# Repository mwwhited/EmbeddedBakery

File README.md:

# Embedded Bakery

## Summary

This is a collection of various electronics and microprocessor projects including PAL, FPGA, CPLD, and microcontroller experiments.

## Repository Structure

```
src/
├── arduino/          # Arduino sketches and libraries
├── AVR/              # AVR microcontroller projects (ATmega, ATtiny)
├── ESP8266/          # ESP8266 WiFi module projects
├── STM32/            # STM32 ARM microcontroller projects
├── PIC/              # Microchip PIC microcontroller projects
├── xilinx/           # Xilinx FPGA projects (Arty A7, Arty Z7)
├── altera/           # Altera/Intel FPGA projects (Cyclone II)
├── GenericFPGA/      # Reusable FPGA IP cores
├── pal/              # Programmable Array Logic projects
├── basicstamp/       # Basic Stamp projects
├── particle/         # Particle IoT projects
└── tools/            # Development tools (.NET solution)
circuits/             # KiCad PCB designs and schematics
notes/                # Reference documentation and datasheets
```

## Key Projects

### Microcontroller Projects
- **Arduino**: Various sensor interfaces, relay controllers, FreeRTOS examples, LANC camera control
- **ESP8266**: LXI Serial Bridge, WiFi relay controllers, network interfaces
- **AVR**: Bare-metal ATmega/ATtiny projects, digital clock
- **STM32**: Blue Pill development projects
- **PIC**: PIC16F627 LED chase patterns

### FPGA Projects
- **Xilinx Arty A7**: MicroBlaze tutorials, custom CPU designs, Pmod interfaces
- **Xilinx Arty Z7**: Zynq HLS tutorials
- **Altera Cyclone II**: Basic FPGA experiments
- **XC9500 CPLD**: Legacy CPLD projects

### PCB Designs
- Analog computer circuits
- Development boards
- Interface adapters (LANC, RS485, H4n)

### Development Tools
- BinaryBaker: ROM/PROM utilities
- MicroCodeBuilder: Custom CPU microcode tools
- TruthExpander: Boolean logic tools

## Getting Started

See individual project README files for specific build instructions.

### Quick Reference

| Platform | Build Tool |
|----------|------------|
| Arduino | Arduino IDE / arduino-cli |
| AVR | WinAVR / avr-gcc + avrdude |
| ESP8266 | PlatformIO / Arduino IDE |
| STM32 | STM32duino / STM32CubeIDE |
| PIC | MPLAB X + XC8 |
| Xilinx | Vivado / ISE |
| Altera | Quartus |
| KiCad | KiCad + KiBot |
| .NET | dotnet CLI / Visual Studio |

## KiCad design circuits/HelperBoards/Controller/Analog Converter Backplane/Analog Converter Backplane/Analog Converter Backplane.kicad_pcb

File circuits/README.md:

# Circuit and PCB Projects

KiCad PCB designs and schematics.

## Projects

### Altair8800
Altair 8800 computer clone PCB.

### AnalogCalculator
Analog computer/calculator circuits including:
- Op-amp based computing boards
- Comdyna GP-6 clone
- Diode function generators
- Fast ADC

### Atmega32DevKit
ATmega32 development kit PCB.

### ComdynaGP6
Comdyna GP-6 analog computer clone components.

### Digital Tools
Digital logic development boards.

### DiodeLogicBoards
Discrete diode logic circuits:
- 1-byte register
- Address decoder (4 to 16)
- Input/output boards
- PROM emulator

### Favero
Favero fencing scoring machine interface.

### HelperBoards
Utility boards:
- 10x10 switch matrix
- Potentiometer boards
- Analog controller boards
- Waveform generator amplifier

### ITT_Phone
Rotary phone interface board.

### MyIOShield
Custom I/O shield PCB.

### Navtec
NavTec interface board.

### Pmod16bitBanked
16-bit banked switch Pmod board.

### PmodLED8x8
8x8 LED matrix Pmod board.

### RC-004 Clone
RC-004 clone circuit.

### SG_Power
Power supply board.

### SimpleClock
Simple clock circuit.

### greaseweazle
Greaseweazle floppy disk interface case/board.

### h4n2rs485
Zoom H4n to RS485 interface.

### i8051
8051 microcontroller development kit.

### lanc2rs485
LANC to RS485 converter.

## KiCad Libraries

### MyCustomSymbols.kicad_sym
Custom schematic symbols.

### MyCustomLibrary.pretty/
Custom PCB footprints.

### KicadSymbols/
Additional symbol libraries.

## Build Documentation

Use KiBot to generate documentation:
```bash
kibot -c ../docs.kibot.yaml
```

## Tools

- **KiCad** - Schematic capture and PCB layout
- **KiBot** - Automated documentation generation

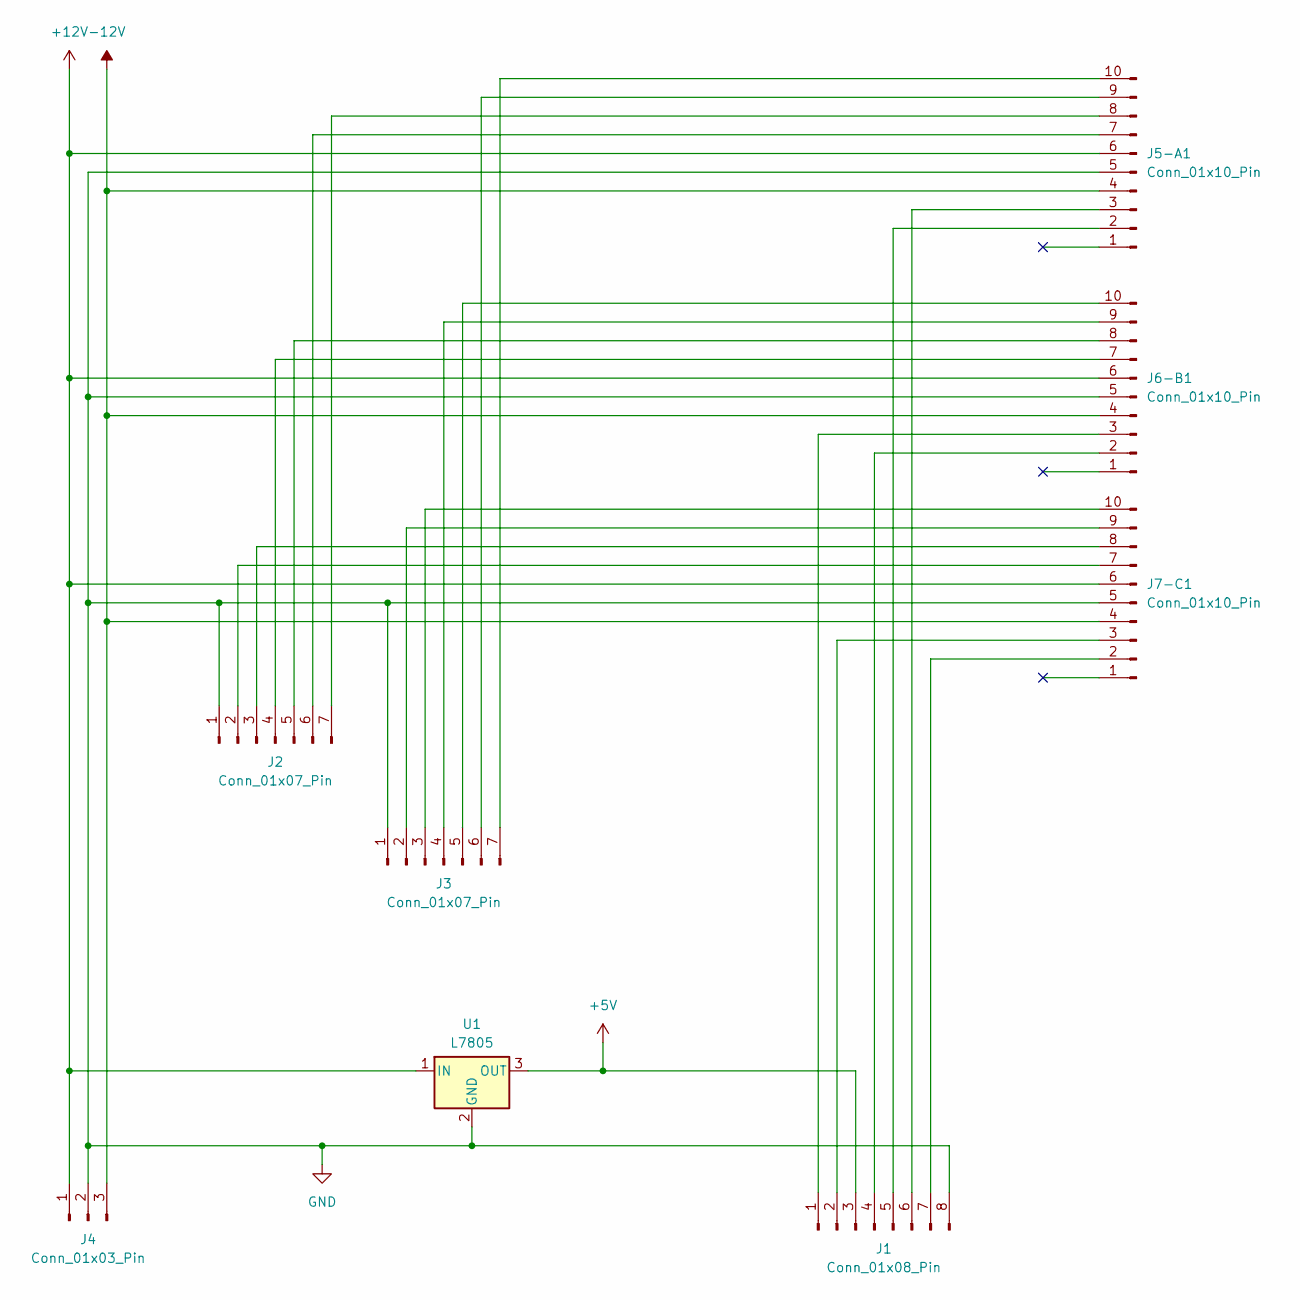
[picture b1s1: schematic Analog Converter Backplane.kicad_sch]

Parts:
J1: Conn_01x08_Pin; PinHeader_1x08_P2.54mm_Vertical
J2, J3: Conn_01x07_Pin; PinHeader_1x07_P2.54mm_Vertical
J4: Conn_01x03_Pin; PinHeader_1x03_P2.54mm_Vertical
J5-A1, J6-B1, J7-C1: Conn_01x10_Pin; PinSocket_1x10_P2.54mm_Vertical
U1: L7805; TO-220-3_Vertical

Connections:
+5V: J1.3, U1.3 (OUT)
+12V: J4.1, J5-A1.6, J6-B1.6, J7-C1.6, U1.1 (IN)
-12V: J4.3, J5-A1.4, J6-B1.4, J7-C1.4
GND: J1.8, J2.1, J3.1, J4.2, J5-A1.5, J6-B1.5, J7-C1.5, U1.2 (GND)
unnamed: J1.1, J6-B1.3
unnamed: J1.2, J7-C1.3
unnamed: J1.4, J6-B1.2
unnamed: J1.5, J5-A1.2
unnamed: J1.6, J5-A1.3
unnamed: J1.7, J7-C1.2
unnamed: J2.2, J7-C1.7
unnamed: J2.3, J7-C1.8
unnamed: J2.4, J6-B1.7
unnamed: J2.5, J6-B1.8
unnamed: J2.6, J5-A1.7
unnamed: J2.7, J5-A1.8
unnamed: J3.2, J7-C1.9
unnamed: J3.3, J7-C1.10
unnamed: J3.4, J6-B1.9
unnamed: J3.5, J6-B1.10
unnamed: J3.6, J5-A1.9
unnamed: J3.7, J5-A1.10

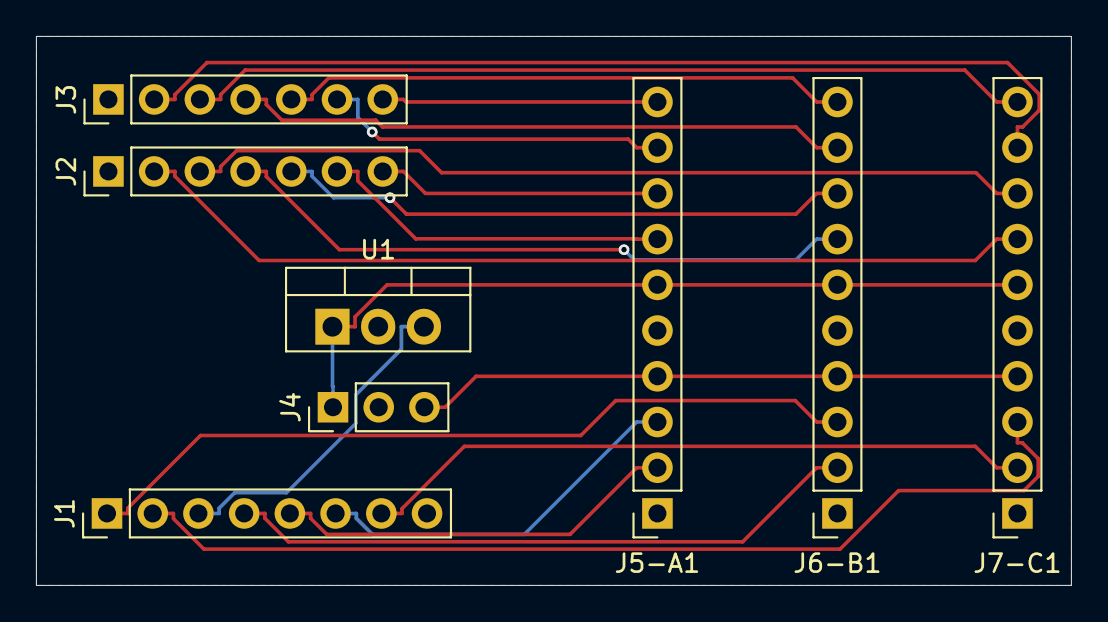
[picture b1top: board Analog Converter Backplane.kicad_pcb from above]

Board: 2 copper layers, 57.5 x 30.5 mm, 8 parts (0 on the bottom side), 22 nets.

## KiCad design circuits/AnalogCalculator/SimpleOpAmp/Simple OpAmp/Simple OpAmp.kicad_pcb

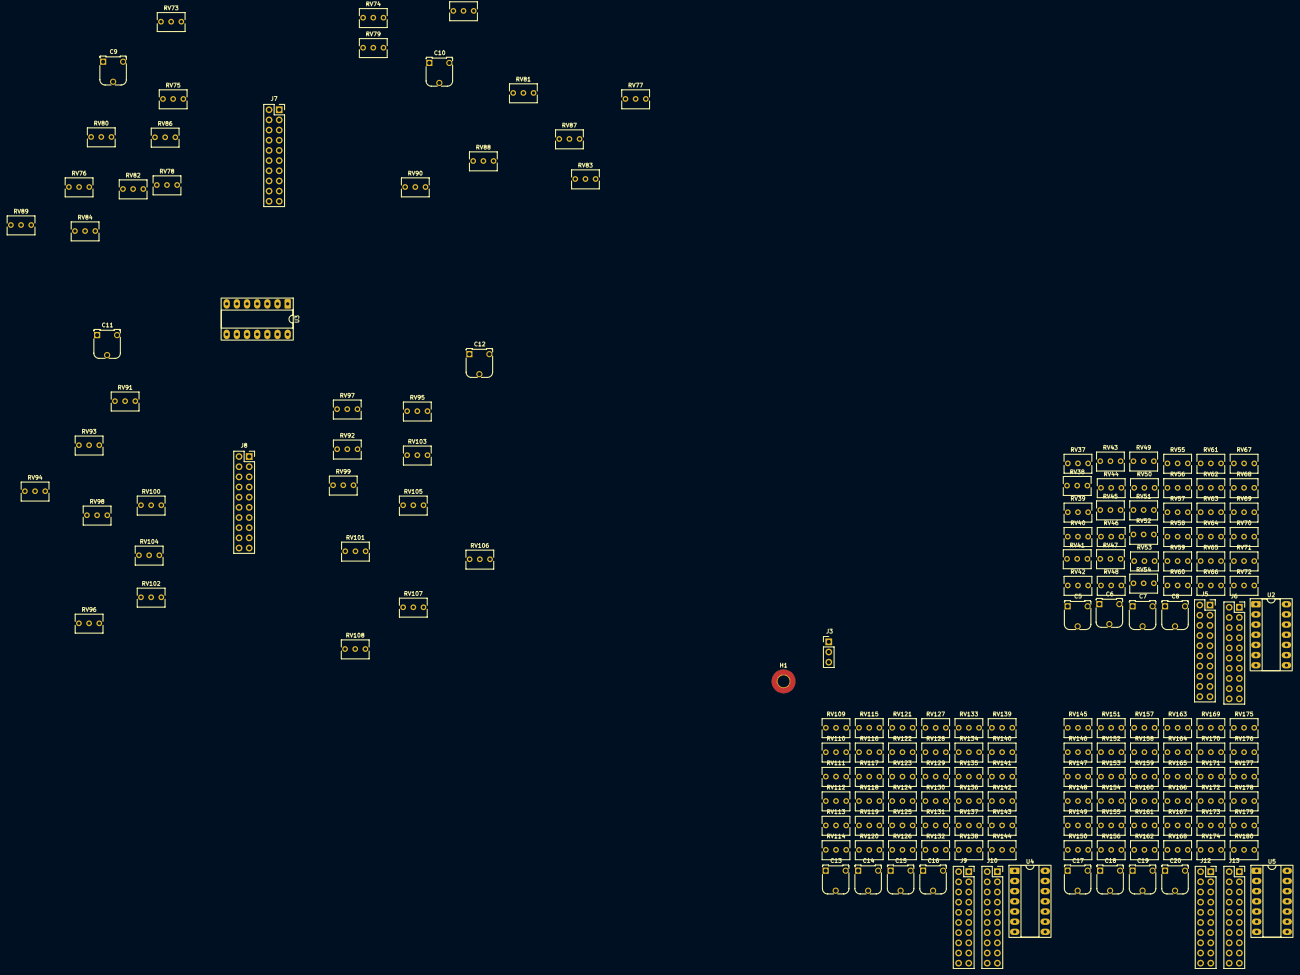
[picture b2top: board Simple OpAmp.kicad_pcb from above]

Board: 2 copper layers, 174 parts (0 on the bottom side), 163 nets, no tracks yet.

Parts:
C5, C6, C7, C8, C9, C10, C11, C12, C13, C14, C15, C16, C17, C18, C19, C20: C_Trim_Differential; Potentiometer_Runtron_RM-065_Vertical
H1: MountingHole_3mm_Pad_TopBottom
J3: Conn_01x03_Pin; PinHeader_1x03_P2.54mm_Vertical
J5, J6, J7, J8, J9, J10, J12, J13: Conn_02x10_Odd_Even; PinSocket_2x10_P2.54mm_Vertical
RV37, RV38, RV39, RV40, RV41, RV42, RV43, RV44, RV45, RV46, RV47, RV48, RV49, RV50, RV51, RV52, RV53, RV54, RV55, RV56, RV57, RV58, RV59, RV60, RV61, RV62, RV63, RV64, RV65, RV66, RV67, RV68, RV69, RV70, RV71, RV72, RV73, RV74, RV75, RV76, RV77, RV78, RV79, RV80, RV81, RV82, RV83, RV84, RV85, RV86, RV87, RV88, RV89, RV90, RV91, RV92, RV93, RV94, RV95, RV96, RV97, RV98, RV99, RV100, RV101, RV102, RV103, RV104, RV105, RV106, RV107, RV108, RV109, RV110, RV111, RV112, RV113, RV114, RV115, RV116, RV117, RV118, RV119, RV120, RV121, RV122, RV123, RV124, RV125, RV126, RV127, RV128, RV129, RV130, RV131, RV132, RV133, RV134, RV135, RV136, RV137, RV138, RV139, RV140, RV141, RV142, RV143, RV144, RV145, RV146, RV147, RV148, RV149, RV150, RV151, RV152, RV153, RV154, RV155, RV156, RV157, RV158, RV159, RV160, RV161, RV162, RV163, RV164, RV165, RV166, RV167, RV168, RV169, RV170, RV171, RV172, RV173, RV174, RV175, RV176, RV177, RV178, RV179, RV180: R_Potentiometer_US; Potentiometer_Bourns_3266Y_Vertical
U2, U3, U4, U5: Opamp_Quad; DIP-14_W7.62mm_Socket_LongPads

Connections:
+15V: J3.1, U2.4 (V+), U3.4 (V+), U4.4 (V+), U5.4 (V+)
-15V: J3.3, U2.11 (V-), U3.11 (V-), U4.11 (V-), U5.11 (V-)
GND: H1.1, J3.2, U2.2 (-), U2.6 (-), U2.9 (-), U2.13 (-), U3.2 (-), U3.6 (-), U3.9 (-), U3.13 (-), U4.2 (-), U4.6 (-), U4.9 (-), U4.13 (-), U5.2 (-), U5.6 (-), U5.9 (-), U5.13 (-)
unnamed: J5.1, RV38.3
unnamed: C5.2, J5.2, RV37.2, U2.7
unnamed: J5.3, RV41.3
unnamed: C5.1, J5.4, RV37.3, RV39.2, RV40.2, RV42.2, RV44.2, RV46.2, RV48.2, RV50.2, RV53.2, U2.5 (+)
unnamed: J5.5, RV43.3
unnamed: J5.6, RV39.3
unnamed: J5.7, RV45.3
unnamed: J5.8, RV40.3
unnamed: J5.9, RV47.3
unnamed: J5.10, RV42.3
unnamed: J5.11, RV49.3
unnamed: J5.12, RV44.3
unnamed: J5.13, RV51.3
unnamed: J5.14, RV46.3
unnamed: J5.15, RV52.3
unnamed: J5.16, RV48.3
unnamed: C6.1, J5.17, RV38.2, RV41.2, RV43.2, RV45.2, RV47.2, RV49.2, RV51.2, RV52.2, RV54.3, U2.3 (+)
unnamed: J5.18, RV50.3
unnamed: C6.2, J5.19, RV54.2, U2.1
unnamed: J5.20, RV53.3
unnamed: J6.1, RV56.3
unnamed: C7.2, J6.2, RV55.2, U2.14
unnamed: J6.3, RV59.3
unnamed: C7.1, J6.4, RV55.3, RV57.2, RV58.2, RV60.2, RV62.2, RV64.2, RV66.2, RV68.2, RV71.2, U2.12 (+)
unnamed: J6.5, RV61.3
unnamed: J6.6, RV57.3
unnamed: J6.7, RV63.3
unnamed: J6.8, RV58.3
unnamed: J6.9, RV65.3
unnamed: J6.10, RV60.3
unnamed: J6.11, RV67.3
unnamed: J6.12, RV62.3
unnamed: J6.13, RV69.3
unnamed: J6.14, RV64.3
unnamed: J6.15, RV70.3
unnamed: J6.16, RV66.3
unnamed: C8.1, J6.17, RV56.2, RV59.2, RV61.2, RV63.2, RV65.2, RV67.2, RV69.2, RV70.2, RV72.3, U2.10 (+)
unnamed: J6.18, RV68.3
unnamed: C8.2, J6.19, RV72.2, U2.8
unnamed: J6.20, RV71.3
unnamed: J7.1, RV74.3
unnamed: C9.2, J7.2, RV73.2, U3.7
unnamed: J7.3, RV77.3
unnamed: C9.1, J7.4, RV73.3, RV75.2, RV76.2, RV78.2, RV80.2, RV82.2, RV84.2, RV86.2, RV89.2, U3.5 (+)
unnamed: J7.5, RV79.3
unnamed: J7.6, RV75.3
unnamed: J7.7, RV81.3
unnamed: J7.8, RV76.3
unnamed: J7.9, RV83.3
unnamed: J7.10, RV78.3
unnamed: J7.11, RV85.3
unnamed: J7.12, RV80.3
unnamed: J7.13, RV87.3
unnamed: J7.14, RV82.3
unnamed: J7.15, RV88.3
unnamed: J7.16, RV84.3
unnamed: C10.1, J7.17, RV74.2, RV77.2, RV79.2, RV81.2, RV83.2, RV85.2, RV87.2, RV88.2, RV90.3, U3.3 (+)
unnamed: J7.18, RV86.3
unnamed: C10.2, J7.19, RV90.2, U3.1
unnamed: J7.20, RV89.3
unnamed: J8.1, RV92.3
unnamed: C11.2, J8.2, RV91.2, U3.14
unnamed: J8.3, RV95.3
unnamed: C11.1, J8.4, RV91.3, RV93.2, RV94.2, RV96.2, RV98.2, RV100.2, RV102.2, RV104.2, RV107.2, U3.12 (+)
unnamed: J8.5, RV97.3
unnamed: J8.6, RV93.3
unnamed: J8.7, RV99.3
unnamed: J8.8, RV94.3
unnamed: J8.9, RV101.3
unnamed: J8.10, RV96.3
unnamed: J8.11, RV103.3
unnamed: J8.12, RV98.3
unnamed: J8.13, RV105.3
unnamed: J8.14, RV100.3
unnamed: J8.15, RV106.3
unnamed: J8.16, RV102.3
unnamed: C12.1, J8.17, RV92.2, RV95.2, RV97.2, RV99.2, RV101.2, RV103.2, RV105.2, RV106.2, RV108.3, U3.10 (+)
unnamed: J8.18, RV104.3
unnamed: C12.2, J8.19, RV108.2, U3.8
unnamed: J8.20, RV107.3
unnamed: J9.1, RV110.3
unnamed: C13.2, J9.2, RV109.2, U4.7
unnamed: J9.3, RV113.3
unnamed: C13.1, J9.4, RV109.3, RV111.2, RV112.2, RV114.2, RV116.2, RV118.2, RV120.2, RV122.2, RV125.2, U4.5 (+)
unnamed: J9.5, RV115.3
unnamed: J9.6, RV111.3
unnamed: J9.7, RV117.3
unnamed: J9.8, RV112.3
unnamed: J9.9, RV119.3
unnamed: J9.10, RV114.3
unnamed: J9.11, RV121.3
unnamed: J9.12, RV116.3
unnamed: J9.13, RV123.3
unnamed: J9.14, RV118.3
unnamed: J9.15, RV124.3
unnamed: J9.16, RV120.3
unnamed: C14.1, J9.17, RV110.2, RV113.2, RV115.2, RV117.2, RV119.2, RV121.2, RV123.2, RV124.2, RV126.3, U4.3 (+)
unnamed: J9.18, RV122.3
unnamed: C14.2, J9.19, RV126.2, U4.1
unnamed: J9.20, RV125.3
unnamed: J10.1, RV128.3
unnamed: C15.2, J10.2, RV127.2, U4.14
unnamed: J10.3, RV131.3
unnamed: C15.1, J10.4, RV127.3, RV129.2, RV130.2, RV132.2, RV134.2, RV136.2, RV138.2, RV140.2, RV143.2, U4.12 (+)
unnamed: J10.5, RV133.3
unnamed: J10.6, RV129.3
unnamed: J10.7, RV135.3
unnamed: J10.8, RV130.3
unnamed: J10.9, RV137.3
unnamed: J10.10, RV132.3
unnamed: J10.11, RV139.3
unnamed: J10.12, RV134.3
unnamed: J10.13, RV141.3
unnamed: J10.14, RV136.3
unnamed: J10.15, RV142.3
unnamed: J10.16, RV138.3
unnamed: C16.1, J10.17, RV128.2, RV131.2, RV133.2, RV135.2, RV137.2, RV139.2, RV141.2, RV142.2, RV144.3, U4.10 (+)
unnamed: J10.18, RV140.3
unnamed: C16.2, J10.19, RV144.2, U4.8
unnamed: J10.20, RV143.3
unnamed: J12.1, RV146.3
unnamed: C17.2, J12.2, RV145.2, U5.7
unnamed: J12.3, RV149.3
unnamed: C17.1, J12.4, RV145.3, RV147.2, RV148.2, RV150.2, RV152.2, RV154.2, RV156.2, RV158.2, RV161.2, U5.5 (+)
unnamed: J12.5, RV151.3
unnamed: J12.6, RV147.3
unnamed: J12.7, RV153.3
unnamed: J12.8, RV148.3
unnamed: J12.9, RV155.3
unnamed: J12.10, RV150.3
unnamed: J12.11, RV157.3
unnamed: J12.12, RV152.3
unnamed: J12.13, RV159.3
unnamed: J12.14, RV154.3
unnamed: J12.15, RV160.3
unnamed: J12.16, RV156.3
unnamed: C18.1, J12.17, RV146.2, RV149.2, RV151.2, RV153.2, RV155.2, RV157.2, RV159.2, RV160.2, RV162.3, U5.3 (+)
unnamed: J12.18, RV158.3
unnamed: C18.2, J12.19, RV162.2, U5.1
unnamed: J12.20, RV161.3
unnamed: J13.1, RV164.3
unnamed: C19.2, J13.2, RV163.2, U5.14
unnamed: J13.3, RV167.3
unnamed: C19.1, J13.4, RV163.3, RV165.2, RV166.2, RV168.2, RV170.2, RV172.2, RV174.2, RV176.2, RV179.2, U5.12 (+)
unnamed: J13.5, RV169.3
unnamed: J13.6, RV165.3
unnamed: J13.7, RV171.3
unnamed: J13.8, RV166.3
unnamed: J13.9, RV173.3
unnamed: J13.10, RV168.3
unnamed: J13.11, RV175.3
unnamed: J13.12, RV170.3
unnamed: J13.13, RV177.3
unnamed: J13.14, RV172.3
unnamed: J13.15, RV178.3
unnamed: J13.16, RV174.3
unnamed: C20.1, J13.17, RV164.2, RV167.2, RV169.2, RV171.2, RV173.2, RV175.2, RV177.2, RV178.2, RV180.3, U5.10 (+)
unnamed: J13.18, RV176.3
unnamed: C20.2, J13.19, RV180.2, U5.8
unnamed: J13.20, RV179.3

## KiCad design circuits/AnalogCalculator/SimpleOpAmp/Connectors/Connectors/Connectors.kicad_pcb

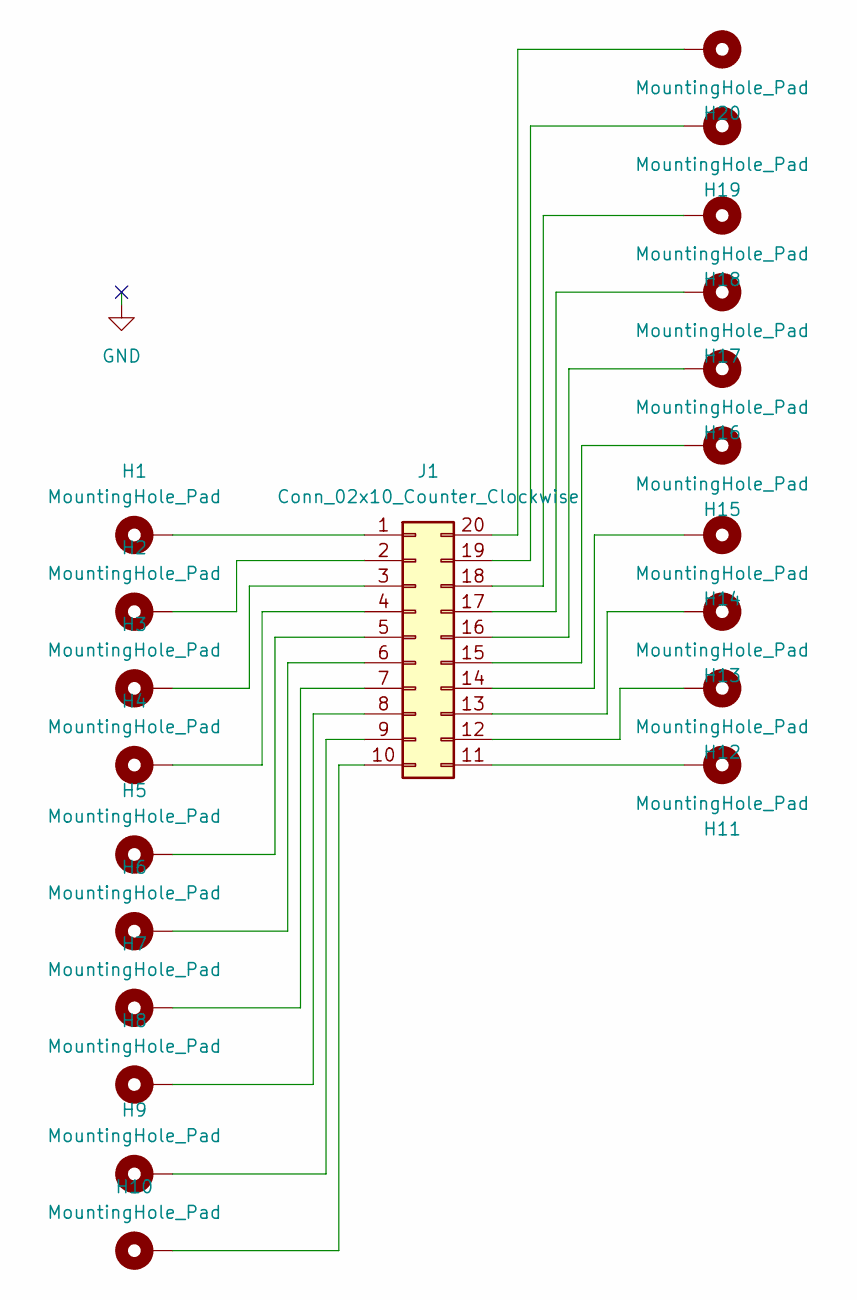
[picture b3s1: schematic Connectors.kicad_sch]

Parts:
H1, H2, H3, H4, H5, H6, H7, H8, H9, H10, H11, H12, H13, H14, H15, H16, H17, H18, H19, H20: MountingHole_Pad; MountingHole_2.2mm_M2_DIN965_Pad
J1: Conn_02x10_Counter_Clockwise; PinHeader_2x10_P2.54mm_Vertical

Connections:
unnamed: H1.1, J1.1
unnamed: H2.1, J1.2
unnamed: H3.1, J1.3
unnamed: H4.1, J1.4
unnamed: H5.1, J1.5
unnamed: H6.1, J1.6
unnamed: H7.1, J1.7
unnamed: H8.1, J1.8
unnamed: H9.1, J1.9
unnamed: H10.1, J1.10
unnamed: H11.1, J1.11
unnamed: H12.1, J1.12
unnamed: H13.1, J1.13
unnamed: H14.1, J1.14
unnamed: H15.1, J1.15
unnamed: H16.1, J1.16
unnamed: H17.1, J1.17
unnamed: H18.1, J1.18
unnamed: H19.1, J1.19
unnamed: H20.1, J1.20

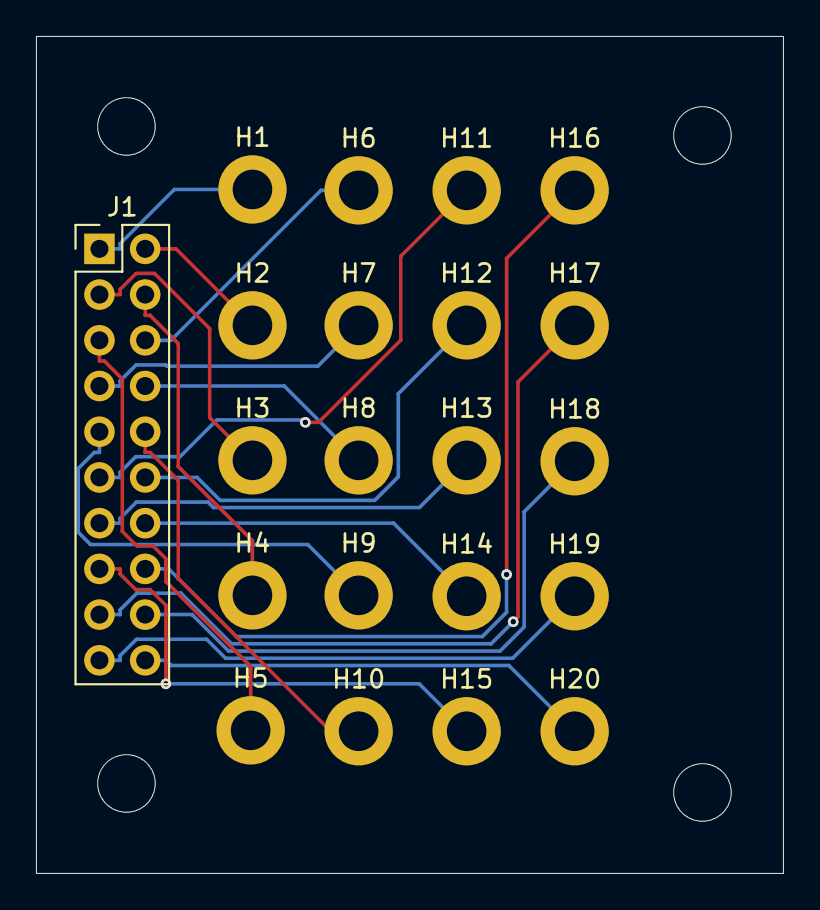
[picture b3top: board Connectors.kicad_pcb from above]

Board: 2 copper layers, 41.5 x 46.5 mm, 25 parts (0 on the bottom side), 20 nets.

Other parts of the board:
REF1, REF2, REF3, REF4: MountingHole_3.2mm_M3

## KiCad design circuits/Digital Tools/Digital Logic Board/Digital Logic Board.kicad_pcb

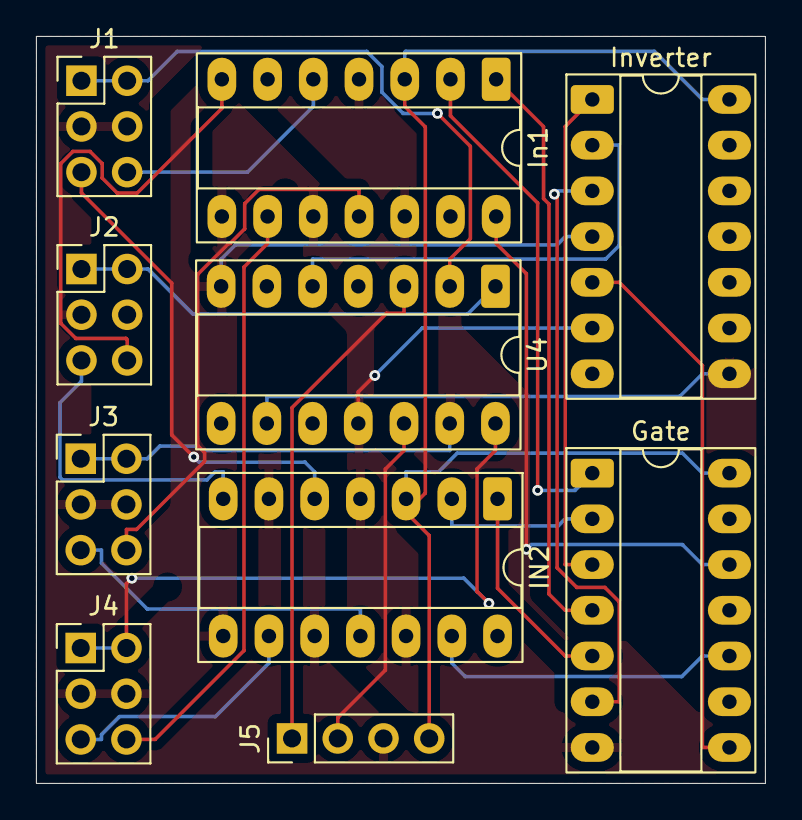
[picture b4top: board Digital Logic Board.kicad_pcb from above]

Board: 2 copper layers, 40.5 x 41.5 mm, 10 parts (0 on the bottom side), 32 nets.

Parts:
Gate: 74LS32; DIP-14_W7.62mm_Socket_LongPads
IN2: LM339; DIP-14_W7.62mm_Socket_LongPads
In1: LM339; DIP-14_W7.62mm_Socket_LongPads
Inverter: 74HC14; DIP-14_W7.62mm_Socket_LongPads
J1, J2, J3, J4: Conn_02x03_Counter_Clockwise; PinHeader_2x03_P2.54mm_Vertical
J5: Conn_01x04_Pin; PinHeader_1x04_P2.54mm_Vertical
U4: LM339; DIP-14_W7.62mm_Socket_LongPads

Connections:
+5V: Gate.14 (VCC), IN2.3 (V+), In1.3 (V+), Inverter.14 (VCC), J5.4
+10V: J5.1, U4.3 (V+)
-10V: J5.2, U4.12 (V-)
GND: Gate.7 (GND), IN2.4 (-), IN2.6 (-), IN2.8 (-), IN2.10 (-), IN2.12 (V-), In1.4 (-), In1.6 (-), In1.8 (-), In1.10 (-), In1.12 (V-), Inverter.7 (GND), Inverter.11, Inverter.13, J1.3, J1.4, J2.3, J2.4, J3.3, J3.4, J4.3, J4.4, J5.3, U4.4 (-), U4.6 (-), U4.8 (-), U4.10 (-)
unnamed: J1.1, J1.2, U4.2
unnamed: IN2.5 (+), J1.5
unnamed: In1.5 (+), J1.6
unnamed: J2.1, J2.2, U4.1
unnamed: IN2.7 (+), J2.5
unnamed: In1.7 (+), J2.6
unnamed: J3.1, J3.2, U4.13
unnamed: IN2.11 (+), J3.5
unnamed: In1.11 (+), J3.6
unnamed: J4.1, J4.2, U4.14
unnamed: IN2.9 (+), J4.5
unnamed: In1.9 (+), J4.6
unnamed: Gate.4, In1.1
unnamed: Gate.1, In1.2
unnamed: Gate.9, In1.13
unnamed: Gate.12, In1.14
unnamed: Gate.3, Inverter.1
unnamed: Gate.6, Inverter.3
unnamed: Gate.8, Inverter.5
unnamed: Gate.11, Inverter.9
unnamed: Gate.5, IN2.1
unnamed: Gate.2, IN2.2
unnamed: Gate.10, IN2.13
unnamed: Gate.13, IN2.14
unnamed: Inverter.2, U4.5 (+)
unnamed: Inverter.4, U4.7 (+)
unnamed: Inverter.6, U4.11 (+)
unnamed: Inverter.8, U4.9 (+)

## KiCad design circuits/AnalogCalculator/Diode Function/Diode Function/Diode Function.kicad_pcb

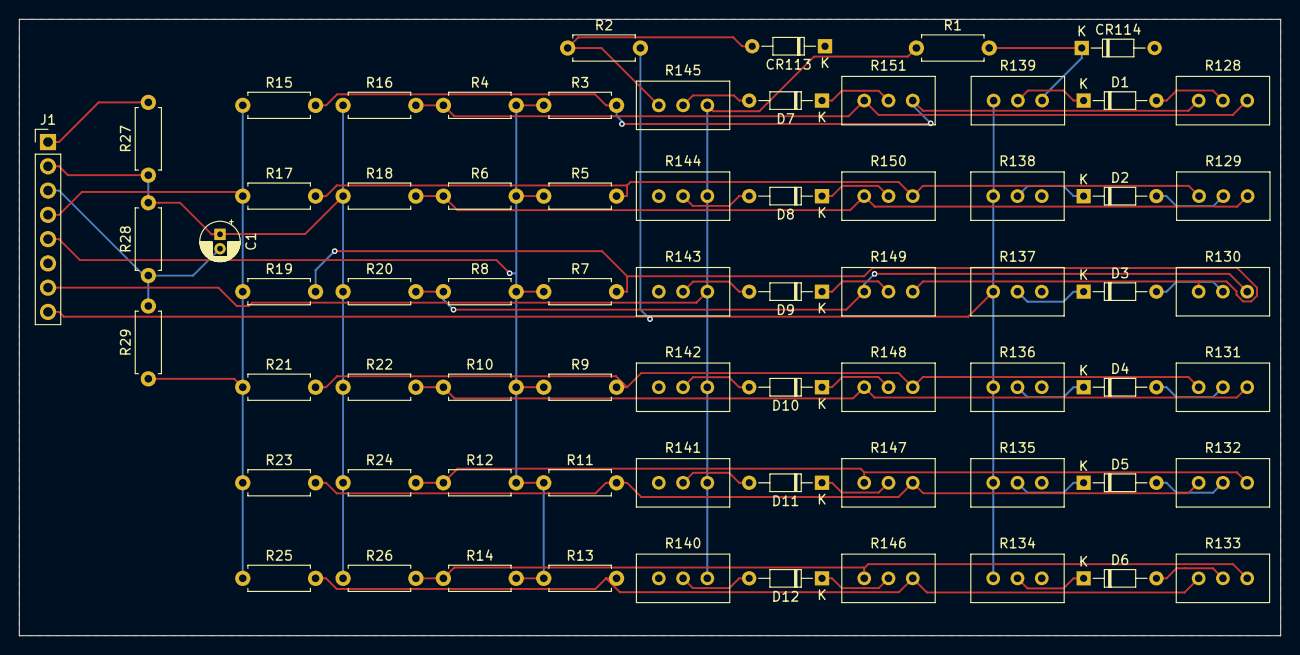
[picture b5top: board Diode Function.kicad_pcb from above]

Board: 2 copper layers, 132.0 x 64.5 mm, 69 parts (0 on the bottom side), 46 nets.

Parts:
C1: 27pF; CP_Radial_D4.0mm_P1.50mm
CR113, CR114: 1N459; D_DO-34_SOD68_P7.62mm_Horizontal
D1, D2, D3, D4, D5, D6, D7, D8, D9, D10, D11, D12: 1N459; D_DO-34_SOD68_P7.62mm_Horizontal
J1: Conn_01x08_Pin; PinHeader_1x08_P2.54mm_Vertical
R1, R2: 68k; R_Axial_DIN0207_L6.3mm_D2.5mm_P7.62mm_Horizontal
R3, R4, R5, R6, R7, R8, R9, R10, R11, R12, R13, R14: 250k; R_Axial_DIN0207_L6.3mm_D2.5mm_P7.62mm_Horizontal
R15, R16, R17, R18, R19, R20, R21, R22, R23, R24, R25, R26: 634k; R_Axial_DIN0207_L6.3mm_D2.5mm_P7.62mm_Horizontal
R27: 1M; R_Axial_DIN0207_L6.3mm_D2.5mm_P7.62mm_Horizontal
R28, R29: 100k; R_Axial_DIN0207_L6.3mm_D2.5mm_P7.62mm_Horizontal
R128, R129, R130, R131, R132, R133, R146, R147, R148, R149, R150, R151: 250k; Potentiometer_Bourns_3296W_Vertical
R134, R135, R136, R137, R138, R139, R140, R141, R142, R143, R144, R145: 100k; Potentiometer_Bourns_3296W_Vertical

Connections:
/+100V: J1.8, R2.2, R134.3, R135.3, R136.3, R137.3, R138.3, R139.3
/-100V: J1.7, R1.1, R140.1, R141.1, R142.1, R143.1, R144.1, R145.1
/Input: J1.5, R3.1, R4.2, R5.1, R6.2, R7.1, R8.2, R9.1, R10.2, R11.1, R12.2, R13.1, R14.2
/Junction 1: J1.4, R15.1, R17.1, R19.1, R21.1, R23.1, R25.1, R29.1
/Junction 2: C1.1, J1.2, R16.1, R18.1, R20.1, R22.1, R24.1, R26.1, R27.1, R28.2
/Output 1: C1.2, J1.3, R28.1, R29.2
/Output 2: J1.1, R27.2
GND: CR113.1 (K), CR114.2 (A), J1.6, R134.1, R135.1, R136.1, R137.1, R138.1, R140.3, R141.3, R142.3, R143.3, R144.3
unnamed: CR113.2 (A), R2.1, R145.3
unnamed: CR114.1 (K), R1.2, R139.1
unnamed: D1.2 (A), R128.2
unnamed: D1.1 (K), R139.2
unnamed: D2.2 (A), R129.2
unnamed: D2.1 (K), R138.2
unnamed: D3.2 (A), R130.2
unnamed: D3.1 (K), R137.2
unnamed: D4.2 (A), R131.2
unnamed: D4.1 (K), R136.2
unnamed: D5.2 (A), R132.2
unnamed: D5.1 (K), R135.2
unnamed: D6.2 (A), R133.2
unnamed: D6.1 (K), R134.2
unnamed: D7.2 (A), R145.2
unnamed: D7.1 (K), R151.2
unnamed: D8.2 (A), R144.2
unnamed: D8.1 (K), R150.2
unnamed: D9.2 (A), R143.2
unnamed: D9.1 (K), R149.2
unnamed: D10.2 (A), R142.2
unnamed: D10.1 (K), R148.2
unnamed: D11.2 (A), R141.2
unnamed: D11.1 (K), R147.2
unnamed: D12.2 (A), R140.2
unnamed: D12.1 (K), R146.2
unnamed: R10.1, R22.2, R131.1, R148.3
unnamed: R11.2, R23.2, R132.3, R147.1
unnamed: R12.1, R24.2, R132.1, R147.3
unnamed: R13.2, R25.2, R133.3, R146.1
unnamed: R4.1, R16.2, R128.1, R151.3
unnamed: R3.2, R15.2, R128.3, R151.1
unnamed: R6.1, R18.2, R129.1, R150.3
unnamed: R5.2, R17.2, R129.3, R150.1
unnamed: R8.1, R20.2, R130.1, R149.3
unnamed: R7.2, R19.2, R130.3, R149.1
unnamed: R9.2, R21.2, R131.3, R148.1
unnamed: R14.1, R26.2, R133.1, R146.3

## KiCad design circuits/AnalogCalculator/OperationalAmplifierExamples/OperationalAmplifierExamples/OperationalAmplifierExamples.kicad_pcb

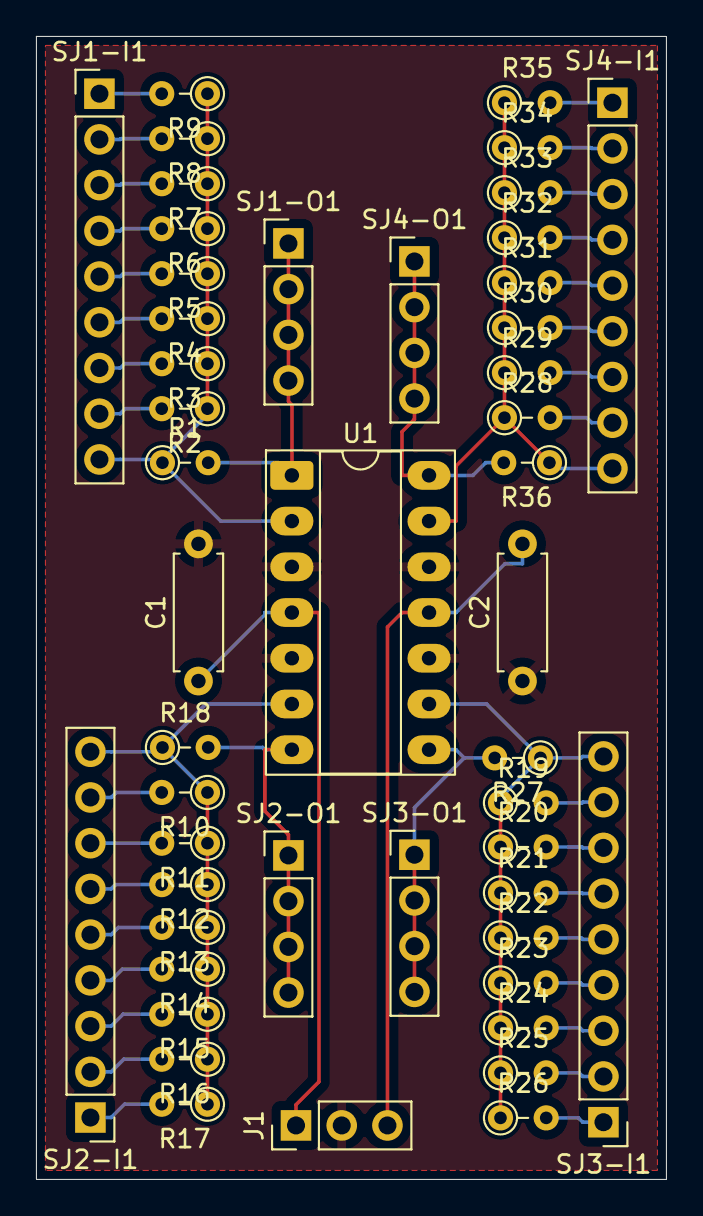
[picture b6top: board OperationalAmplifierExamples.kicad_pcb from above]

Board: 2 copper layers, 35.0 x 63.5 mm, 48 parts (0 on the bottom side), 43 nets.

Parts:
C1, C2: 100nf; R_Axial_DIN0207_L6.3mm_D2.5mm_P7.62mm_Horizontal
J1: Conn_01x03_Pin; PinHeader_1x03_P2.54mm_Vertical
R1, R2, R3, R4, R5, R10, R11, R12, R13, R18, R19, R20, R21, R22, R27, R28, R29, R30, R31, R36: 100k; R_Axial_DIN0204_L3.6mm_D1.6mm_P2.54mm_Vertical
R6, R7, R14, R15, R23, R24, R32, R33: 10k; R_Axial_DIN0204_L3.6mm_D1.6mm_P2.54mm_Vertical
R8, R9, R16, R17, R25, R26, R34, R35: 1M; R_Axial_DIN0204_L3.6mm_D1.6mm_P2.54mm_Vertical
SJ1-I1, SJ2-I1, SJ3-I1, SJ4-I1: Conn_01x09; PinHeader_1x09_P2.54mm_Vertical
SJ1-O1, SJ2-O1, SJ3-O1, SJ4-O1: Conn_01x04_Pin; PinHeader_1x04_P2.54mm_Vertical
U1: LM324; DIP-14_W7.62mm_Socket_LongPads

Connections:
+15V: C1.1, J1.1, U1.4 (V+)
-15V: C2.2, J1.3, U1.11 (V-)
/Inverting Summer/S1-1-1: R2.2, SJ1-I1.8
/Inverting Summer/S1-1-2: R3.2, SJ1-I1.7
/Inverting Summer/S1-1-3: R4.2, SJ1-I1.6
/Inverting Summer/S1-1-4: R5.2, SJ1-I1.5
/Inverting Summer/S1-10-7: R8.2, SJ1-I1.2
/Inverting Summer/S1-10-8: R9.2, SJ1-I1.1
/Inverting Summer/S1-.1-5: R6.2, SJ1-I1.4
/Inverting Summer/S1-.1-6: R7.2, SJ1-I1.3
/Inverting Summer/S1-Out: R1.2, SJ1-O1.1, SJ1-O1.2, SJ1-O1.3, SJ1-O1.4, U1.1
/Inverting Summer/S1-SJ: R1.1, R2.1, R3.1, R4.1, R5.1, R6.1, R7.1, R8.1, R9.1, SJ1-I1.9, U1.2 (-)
/Inverting Summer/S2-1-1: R10.2, SJ2-I1.8
/Inverting Summer/S2-1-2: R11.2, SJ2-I1.7
/Inverting Summer/S2-1-3: R12.2, SJ2-I1.6
/Inverting Summer/S2-1-4: R13.2, SJ2-I1.5
/Inverting Summer/S2-10-7: R16.2, SJ2-I1.2
/Inverting Summer/S2-10-8: R17.2, SJ2-I1.1
/Inverting Summer/S2-.1-5: R14.2, SJ2-I1.4
/Inverting Summer/S2-.1-6: R15.2, SJ2-I1.3
/Inverting Summer/S2-Out: R18.2, SJ2-O1.1, SJ2-O1.2, SJ2-O1.3, SJ2-O1.4, U1.7
/Inverting Summer/S2-SJ: R10.1, R11.1, R12.1, R13.1, R14.1, R15.1, R16.1, R17.1, R18.1, SJ2-I1.9, U1.6 (-)
/Inverting Summer/S3-1-1: R19.2, SJ3-I1.8
/Inverting Summer/S3-1-2: R20.2, SJ3-I1.7
/Inverting Summer/S3-1-3: R21.2, SJ3-I1.6
/Inverting Summer/S3-1-4: R22.2, SJ3-I1.5
/Inverting Summer/S3-10-7: R25.2, SJ3-I1.2
/Inverting Summer/S3-10-8: R26.2, SJ3-I1.1
/Inverting Summer/S3-.1-5: R23.2, SJ3-I1.4
/Inverting Summer/S3-.1-6: R24.2, SJ3-I1.3
/Inverting Summer/S3-Out: R27.2, SJ3-O1.1, SJ3-O1.2, SJ3-O1.3, SJ3-O1.4, U1.8
/Inverting Summer/S3-SJ: R19.1, R20.1, R21.1, R22.1, R23.1, R24.1, R25.1, R26.1, R27.1, SJ3-I1.9, U1.9 (-)
/Inverting Summer/S4-1-1: R28.2, SJ4-I1.8
/Inverting Summer/S4-1-2: R29.2, SJ4-I1.7
/Inverting Summer/S4-1-3: R30.2, SJ4-I1.6
/Inverting Summer/S4-1-4: R31.2, SJ4-I1.5
/Inverting Summer/S4-10-7: R34.2, SJ4-I1.2
/Inverting Summer/S4-10-8: R35.2, SJ4-I1.1
/Inverting Summer/S4-.1-5: R32.2, SJ4-I1.4
/Inverting Summer/S4-.1-6: R33.2, SJ4-I1.3
/Inverting Summer/S4-Out: R36.2, SJ4-O1.1, SJ4-O1.2, SJ4-O1.3, SJ4-O1.4, U1.14
/Inverting Summer/S4-SJ: R28.1, R29.1, R30.1, R31.1, R32.1, R33.1, R34.1, R35.1, R36.1, SJ4-I1.9, U1.13 (-)
GND: C1.2, C2.1, J1.2, U1.3 (+), U1.5 (+), U1.10 (+), U1.12 (+)

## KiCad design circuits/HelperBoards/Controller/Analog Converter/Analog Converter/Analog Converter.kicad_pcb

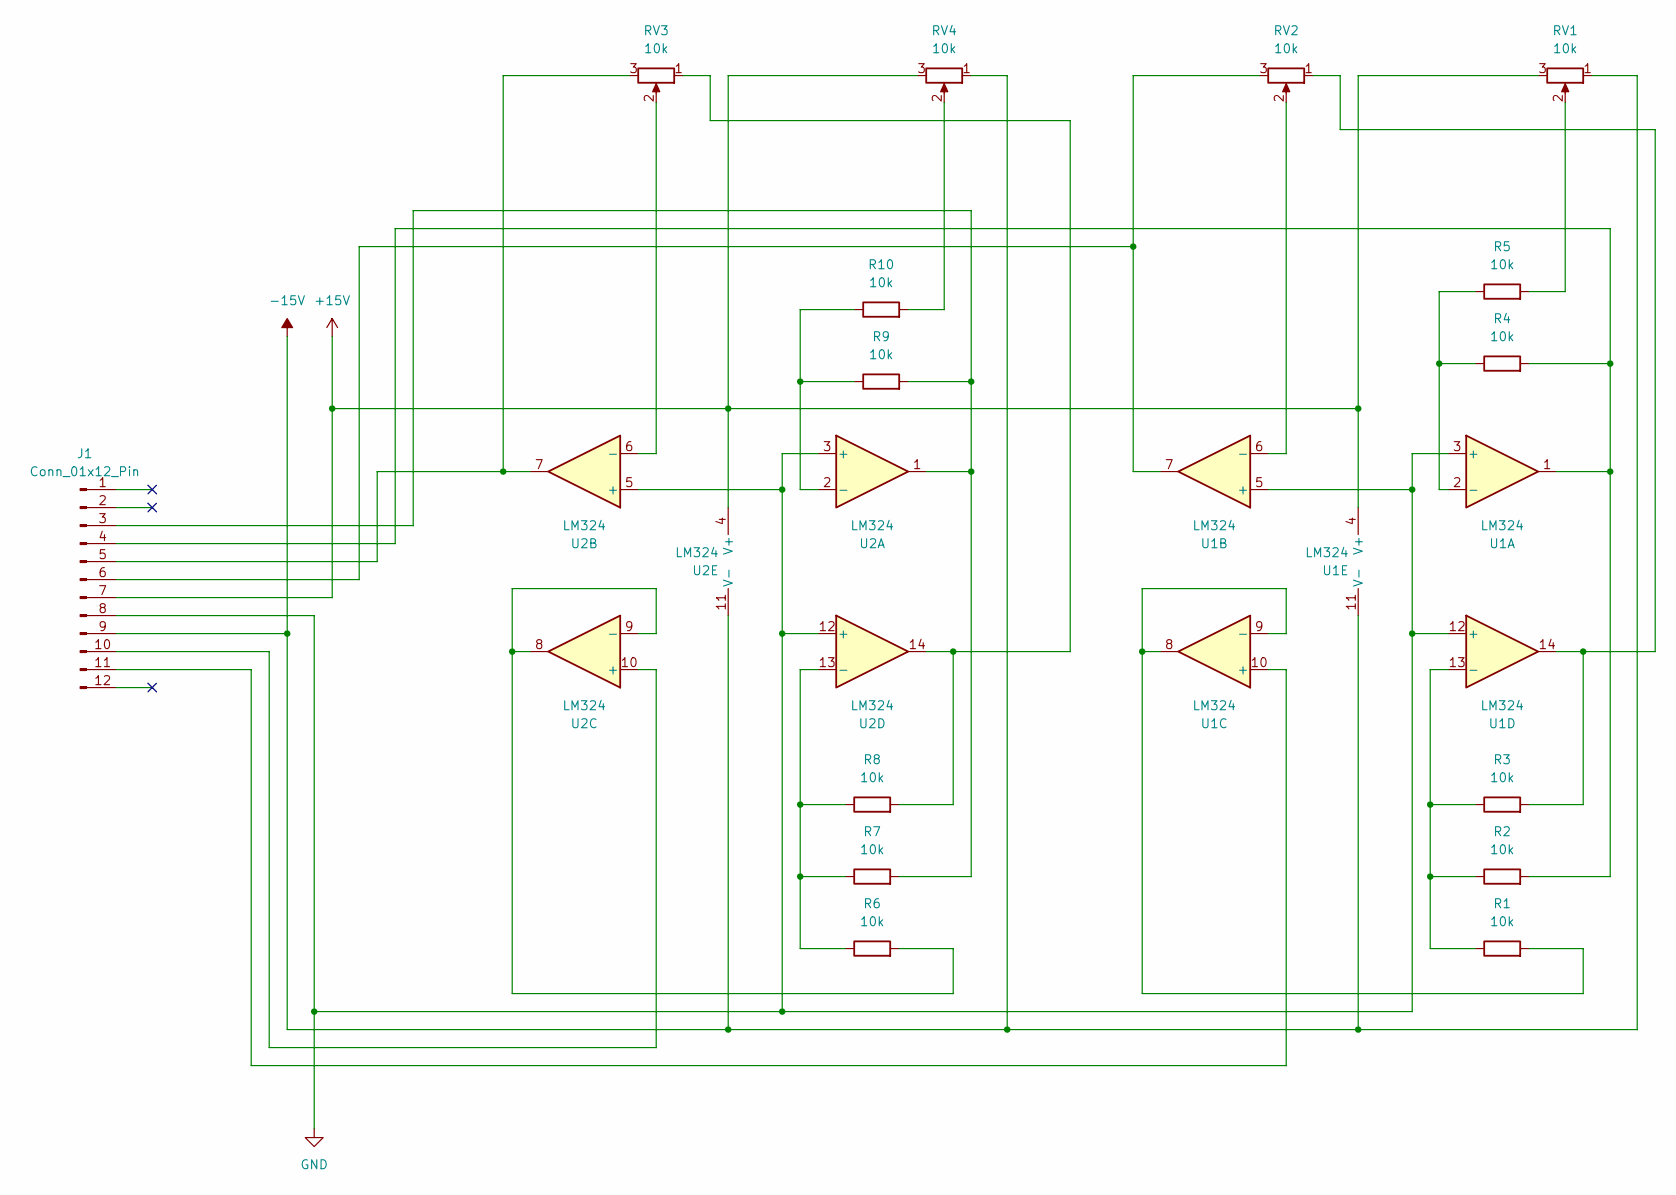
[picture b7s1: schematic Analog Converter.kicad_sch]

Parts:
J1: Conn_01x12_Pin; PinHeader_1x12_P2.54mm_Vertical
R1, R2, R3, R4, R5, R6, R7, R8, R9, R10: 10k; R_Axial_DIN0204_L3.6mm_D1.6mm_P2.54mm_Vertical
RV1, RV2, RV3, RV4: 10k; Potentiometer_Vishay_T93YA_Vertical
U1, U2: LM324; DIP-14_W7.62mm_Socket_LongPads

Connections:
+15V: J1.7, RV1.3, RV4.3, U1.4 (V+), U2.4 (V+)
-15V: J1.9, RV1.1, RV4.1, U1.11 (V-), U2.11 (V-)
GND: J1.8, U1.3 (+), U1.5 (+), U1.12 (+), U2.3 (+), U2.5 (+), U2.12 (+)
unnamed: J1.3, R7.2, R9.2, U2.1
unnamed: J1.4, R2.2, R4.2, U1.1
unnamed: J1.5, RV3.3, U2.7
unnamed: J1.6, RV2.3, U1.7
unnamed: J1.10, U2.10 (+)
unnamed: J1.11, U1.10 (+)
unnamed: R3.2, RV2.1, U1.14
unnamed: R5.2, RV1.2
unnamed: R8.2, RV3.1, U2.14
unnamed: R10.2, RV4.2
unnamed: R4.1, R5.1, U1.2 (-)
unnamed: RV2.2, U1.6 (-)
unnamed: R1.2, U1.8, U1.9 (-)
unnamed: R1.1, R2.1, R3.1, U1.13 (-)
unnamed: R9.1, R10.1, U2.2 (-)
unnamed: RV3.2, U2.6 (-)
unnamed: R6.2, U2.8, U2.9 (-)
unnamed: R6.1, R7.1, R8.1, U2.13 (-)

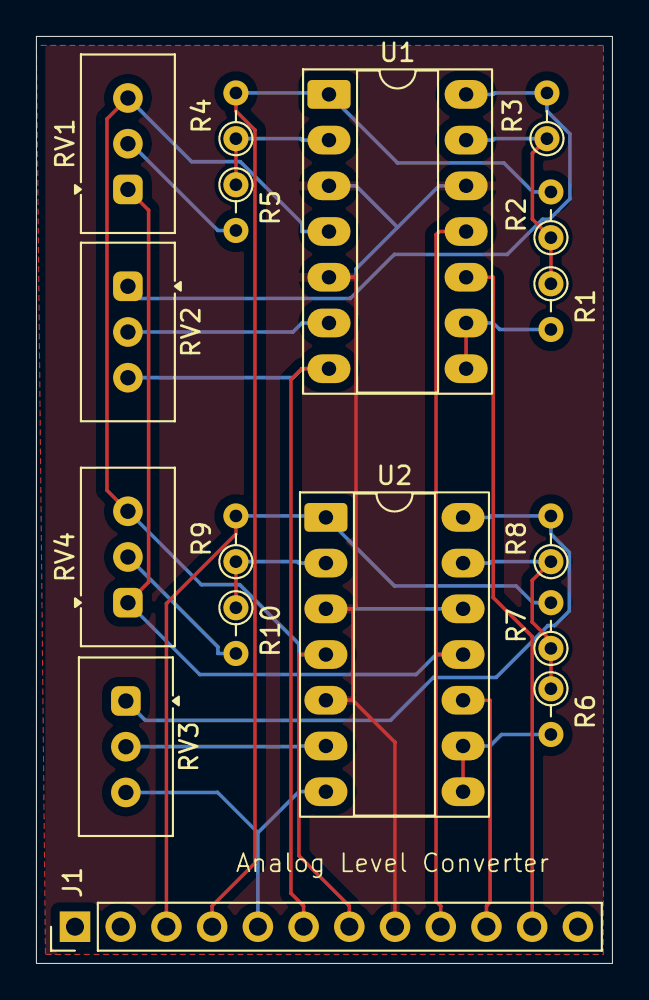
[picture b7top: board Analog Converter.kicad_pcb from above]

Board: 2 copper layers, 32.0 x 51.5 mm, 17 parts (0 on the bottom side), 21 nets.
